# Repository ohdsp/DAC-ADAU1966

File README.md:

# [Open Hardware DSP Platform](http://www.ohdsp.org)
## ADAU1966 DAC with passive output filters
### Revision 2.0
###### DAC-ADAU1966 (KiCad 4.0.2-stable)
---
# README
### Disclaimer
Copyright Paul Janicki 2016

Licensed under the TAPR Open Hardware License (www.tapr.org/OHL)

This documentation is distributed WITHOUT ANY EXPRESS OR IMPLIED WARRANTY, INCLUDING OF MERCHANTABILITY, SATISFACTORY QUALITY AND FITNESS FOR A PARTICULAR PURPOSE.

### What is this repository? ###

**Quick summary**

This is a digital to analogue converter based on the ADAU1966 DAC chip from Analog Devices. This is designed as part the Open Hardware DSP Platform. This may or may not be suitable for use in other applications. 

This simple 16 channel DAC is designed to be used with 4xTDM4, 2xTDM8 or 1xTDM16 data inputs supported on devices such as the ADAU1452. This board can be used with the ADAU1966 in standalone mode (no host microcontroller needed) or with an external I2C interface to program/control the ADAU1966. The board uses only passive output filters on the ADAU1966 but can easily drive external PCBs through appropriate cabling.

This repository contains the KiCad design files, manufacturing Gerber/drill files, and PDF/drawing files for this board.

### What is the project folder structure?
Most folder names are self explanatory. Starting from the top level: \
*DAC-ADAU1966*
+ *Bill of Materials*  - This contains the bill of materials in CVS, LibreOffice Calc and XML formats
+ *Drawings*
    + *PCB* - This contains SVG and PDF outputs of PCB copper layers and assembly drawings
    + *Schematics* - This contains the PDF schematic drawing
+ *Gerbers* - This contains the PCB Gerbers and drill drawings for manufacture, there is also a zip file ready to send to most manufacturers
+ *KiCad* - This contains the original KiCad schematic and PCB design files

### How do I get set up? ###

**Summary of set up**

1. Set your self up a directory on a local disk, something simple will make life easier (eg C:\Electronics on Windows as used here), but anywhere will do just fine.
2. Download the Kicad-Libs from [https://github.com/ohdsp/KiCad-Libs](https://github.com/ohdsp/KiCad-Libs) and place in C:\Electronics\Kicad-Libs (or your chosen folder) 
3. Create a OHDSP subdirectory in C:\Electronics (so C:\Electronics\OHDSP)
3. Download this project to C:\Electronics\OHDSP\DAC-ADAU1966
4. Fire up Kicad
5. Open the main project file C:\Electronics\OHDSP\DAC-ADAU1966\Schematics\DAC-ADAU1966.pro
6. (Optional) Setup Pcbnew component library as below.
7. Do as you wish with the project, just keep it under the TAPR Open Hardware License.

Make sure your git setup doesn't exclude files used in the project (like .LIB files) or things may go wrong down the line.

**KiCad Library Configuration**

Note that you need to setup a Pcbnew library, but the eeschema libraries should work without any changes if you followed the instructions above.

To setup Pcbnew libraries:

In Pcbnew go to Preferences -> Footprint Libraries Manager. Under Global Libraries tab in the top list check if there is a nickname "MyKiCadLibs-Footprints" (usually at the end of the list). If there is but it points to the wrong place then change the Library Path to point to MyKiCadLibs-Footprints (eg C:\Electronics\KiCad-Libs\MyKiCadLibs-Footprints.pretty) folder for your setup. If this is missing you can use "Append with Wizard", choose "Files on my computer", click next, browse to library location (eg C:\Electronics\KiCad-Libs\MyKiCadLibs-Footprints.pretty) and select the folder MyKiCadLibs-Footprints.pretty, click next, check the Status column states OK and the Format is KiCad (if not re-download the library) and click next, then select "To global library configuration..." and click Finish.

To setup eeschema component libraries:
Either from KiCad project window go to Tools -> Run Library Editor OR under eeschema, go to Tools -> Library Editor. Then Preferences -> Component Libraries.

The top section "Component Library Files" should ideally contain only two libraries, the "power" library that ships with KiCad and "MyKiCadLibs-Lib" available from above. To setup MyKiCadLibs-Lib as a relative path under the "User defined search path" click add. Browse to the location of KiCad-Libs you download above (eg C:\Electronics\KiCad-Libs) and click "Select Folder". Say yes to add a relative path. Under component library files click add, browse to the KiCad-libs again (eg C:\Electronics\KiCad-Libs), select file "MyKiCadLibs-Lib.lib" and click open. MyKiCadLibs-lib should appear in the component library list with no path as it will be using the user defined search path set in the box below.

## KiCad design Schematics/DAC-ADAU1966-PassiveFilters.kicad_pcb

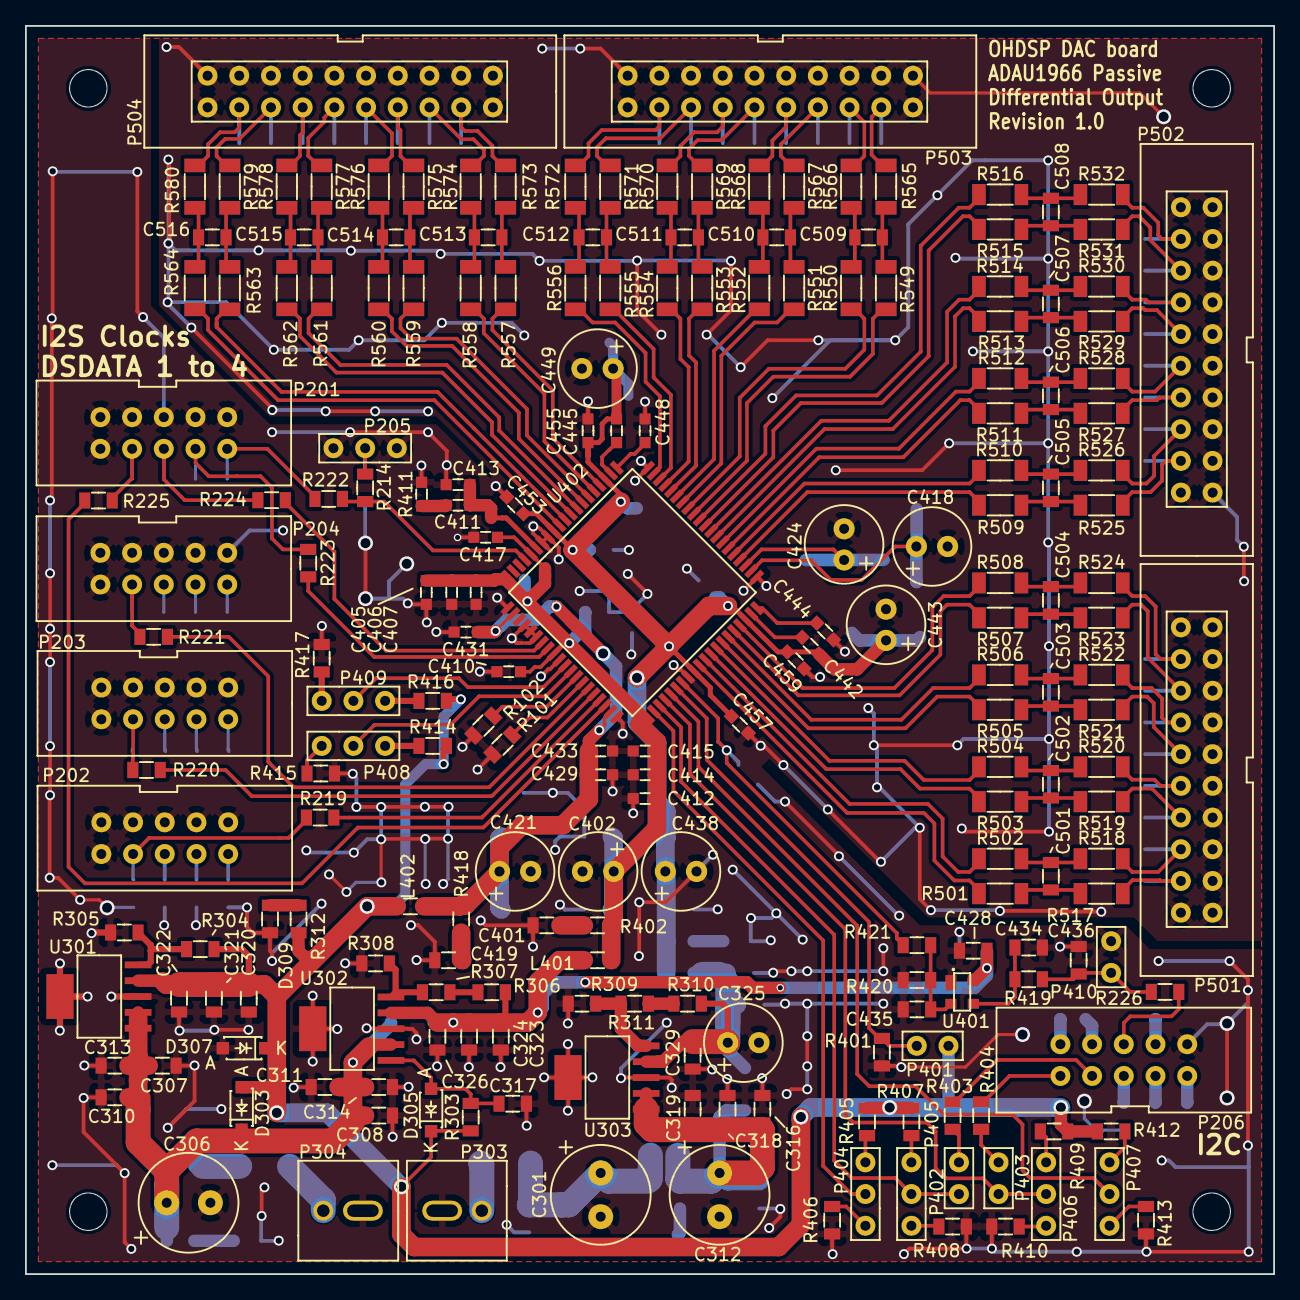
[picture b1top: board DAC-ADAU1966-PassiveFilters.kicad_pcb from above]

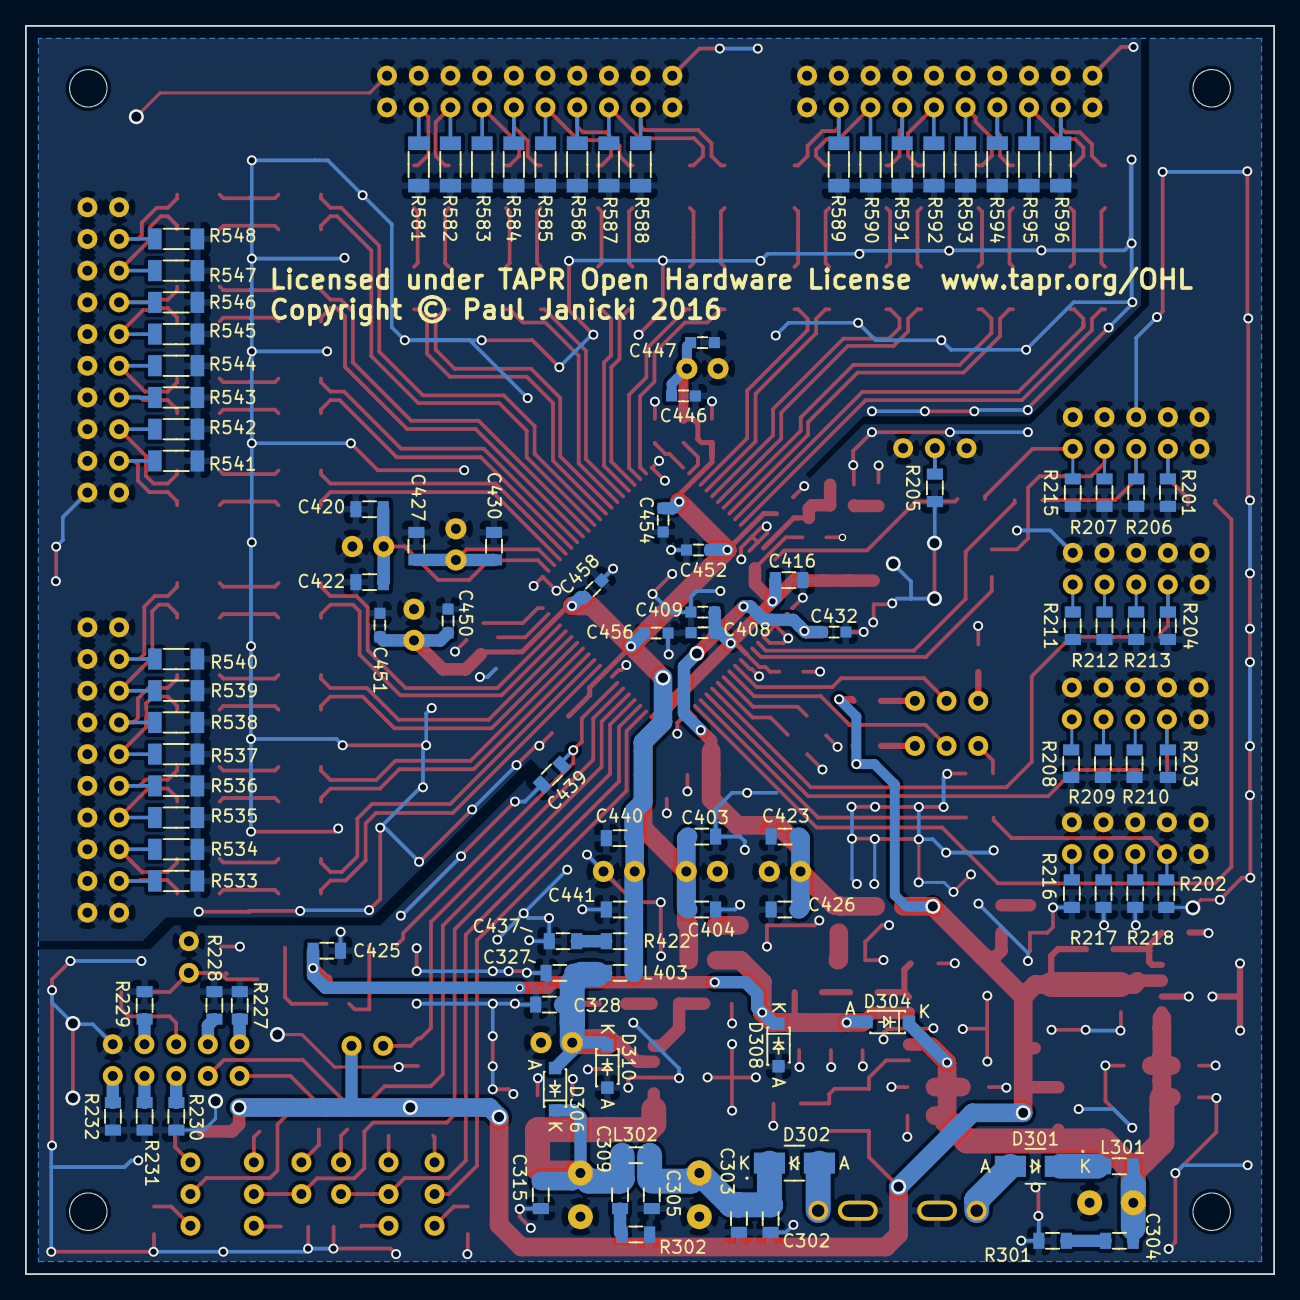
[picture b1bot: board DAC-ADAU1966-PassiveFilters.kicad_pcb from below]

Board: 2 copper layers, 100.0 x 100.0 mm, 314 parts (100 on the bottom side), 189 nets.

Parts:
C301, C306, C312: 220u; CAP-TH-D8mmP3.5mm
C302, C307, C308, C315, C317, C320, C323, C327, C403, C416, C420, C423, C427, C440: 22u; SMD-0805
C303, C310, C311, C316, C321, C324, C328, C404, C422, C426, C428, C430, C434, C435, C436, C439, C441: 100n; SMD-0805
C304, C309, C401, C419, C437: 100p; SMD-0805
C305, C313, C314, C318, C322, C326, C329: 10n; SMD-0805
C319: 1n; SMD-0805
C325, C402, C418, C421, C424, C438: 220u; CAP-TH-D6.3mmP2.5mm
C405, C408, C412, C429, C432, C452, C454, C456, C458: 1u; SMD-0603
C406, C409, C414, C417, C431, C433, C446, C450, C453, C455, C457, C459: 100n; SMD-0603
C407, C410, C415, C447, C451: 10n; SMD-0603
C411: 5n6; SMD-0603
C413: 390p; SMD-0603
C425: 1u; SMD-0805
C442, C444, C445, C448: 470n; SMD-0603
C443, C449: 47u; CAP-TH-D6.3mmP2.5mm
C501, C502, C503, C504, C505, C506, C507, C508, C509, C510, C511, C512, C513, C514, C515, C516: 2n7; SMD-0805
D301, D302: B230A; DIODE-SMA
D303, D304, D306, D307, D308, D310: SBR1A40S1; DIODE-SOD-123
D305: B130LAW-7-F; DIODE-SOD-123
D309: LED; SMD-0805
L301, L302, L401, L402, L403: 600R@100MHz; SMD-0805
P201, P202, P203, P204, P206: CONN_02X05; CONN_DIL_2X5_BOX
P205, P404, P405, P406, P407, P408, P409: CONN_3x1; CONN_SIL_3
P301, P302, P305, P306: PIN; MountingHole_3mm
P303, P304: CONN_2x1; CONN-2WAY-2.54mm-3.81mm-SPACING
P401, P402, P403, P410: CONN_2x1; CONN_SIL_2
P501, P502, P503, P504: CONN_02X10; CONN_DIL_2X10_BOX
R101, R102, R419: 1k; SMD-0805
R201, R202, R203, R204, R205, R206, R207, R214, R215, R305: N/F; SMD-0805
R208, R209, R210, R211, R212, R213, R216, R217, R218, R401, R405, R406, R407, R408, R409, R410, R412, R413, R414, R415, R416, R417: 10k; SMD-0805
R219, R220, R221, R222, R223, R224, R225, R226, R227, R228, R229, R230, R231, R232, R304, R310, R403, R404: 0R; SMD-0805
R301, R302, R402, R418, R422: 47R; SMD-0805
R303: 47k; SMD-0805
R306, R309: 2k2; SMD-0805
R307: 2k7; SMD-0805
R308: 4k7; SMD-0805
R311: 6k8; SMD-0805
R312: 470; SMD-0805
R411: 562R; SMD-0603
R420: 100k; SMD-0805
R421: 100R; SMD-0805
R501, R502, R503, R504, R505, R506, R507, R508, R509, R510, R511, R512, R513, R514, R515, R516, R549, R550, R551, R552, R553, R554, R555, R556, R557, R558, R559, R560, R561, R562, R563, R564: 240; SMD-1206
R517, R518, R519, R520, R521, R522, R523, R524, R525, R526, R527, R528, R529, R530, R531, R532, R565, R566, R567, R568, R569, R570, R571, R572, R573, R574, R575, R576, R577, R578, R579, R580: 100R; SMD-1206
R533, R534, R535, R536, R537, R538, R539, R540, R541, R542, R543, R544, R545, R546, R547, R548, R581, R582, R583, R584, R585, R586, R587, R588, R589, R590, R591, R592, R593, R594, R595, R596: 100k; SMD-1206
U301: TPS7A4533; IC-SOT223-6
U302, U303: TPS7A4501; IC-SOT223-6
U401: ADM811ZART; IC-SOT143
U402: IC-DAC-ADAU1966; IC-LQFP80-P065

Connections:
/ADAU1966/AVDD: C438.1, C440.1, C441.1, C442.1, C443.1, C445.1, C446.1, C447.1, C449.1, C450.1, C451.1, C452.1, C453.1, C454.1, C455.1, C456.1, C457.1, C458.1, C459.1, L403.2, R422.1, U402.3, U402.12, U402.49, U402.58
/ADAU1966/CCLK/SCL: P403.2, P406.2, U402.44
/ADAU1966/CDATA/ADDR1: P404.2, U402.42
/ADAU1966/COUT/SDA: P402.2, P405.2, U402.43
/ADAU1966/DACOUT_LRCLK: R223.2, U402.28
/ADAU1966/DACOUT_SDATA1: R225.2, U402.38
/ADAU1966/DACOUT_SDATA2: R219.2, U402.37
/ADAU1966/DACOUT_SDATA3: R220.2, U402.36
/ADAU1966/DACOUT_SDATA4: R221.2, U402.35
/ADAU1966/DACOUT_SDATA5: R101.1, U402.34
/ADAU1966/DACOUT_SDATA6: R102.1, U402.33
/ADAU1966/DAC_RESET: C439.1, R421.1, U402.47
/ADAU1966/DAC_SCL: P206.1, R404.1
/ADAU1966/DAC_SDA: P206.3, R403.1
/ADAU1966/DSDATA7: P408.2, U402.32
/ADAU1966/DSDATA8: P409.2, U402.31
/ADAU1966/DVDD: C402.1, C403.1, C404.1, C405.1, C406.1, C407.1, C408.1, C409.1, C410.1, C412.1, C414.1, C415.1, C416.1, C417.1, L401.2, R402.1, U402.16, U402.20, U402.29, U402.41
/ADAU1966/IOVDD: C421.1, C423.1, C426.1, C429.1, C431.1, C432.1, C433.1, L402.2, R418.1, U402.22, U402.39
/ADAU1966/LF: C411.1, C413.1, U402.15
/ADAU1966/MAN_RST_IN: C436.1, P410.1, R226.2, R419.2
/ADAU1966/MCLK: R214.2, R222.2, U402.17
/ADAU1966/OUT_1P: R501.1, U402.50
/ADAU1966/OUT_2P: R503.1, U402.52
/ADAU1966/OUT_3P: R505.1, U402.54
/ADAU1966/OUT_4P: R507.1, U402.56
/ADAU1966/OUT_5P: R509.1, U402.64
/ADAU1966/OUT_6P: R511.1, U402.66
/ADAU1966/OUT_7P: R513.1, U402.68
/ADAU1966/OUT_8P: R515.1, U402.70
/ADAU1966/OUT_9P: R549.1, U402.72
/ADAU1966/OUT_10P: R551.1, U402.74
/ADAU1966/OUT_11P: R553.1, U402.76
/ADAU1966/OUT_12P: R555.1, U402.78
/ADAU1966/OUT_13P: R557.1, U402.4
/ADAU1966/OUT_14P: R559.1, U402.6
/ADAU1966/OUT_15P: R561.1, U402.8
/ADAU1966/OUT_16P: R563.1, U402.10
/ADAU1966/SA: P401.2, R401.1, U402.46
/ADAU1966/~SS~/ADDR0: P407.2, U402.45
/AnaloguePassiveFilters/N1: R502.1, U402.51
/AnaloguePassiveFilters/N2: R504.1, U402.53
/AnaloguePassiveFilters/N3: R506.1, U402.55
/AnaloguePassiveFilters/N4: R508.1, U402.57
/AnaloguePassiveFilters/N5: R510.1, U402.65
/AnaloguePassiveFilters/N6: R512.1, U402.67
/AnaloguePassiveFilters/N7: R514.1, U402.69
/AnaloguePassiveFilters/N8: R516.1, U402.71
/AnaloguePassiveFilters/N9: R550.1, U402.73
/AnaloguePassiveFilters/N10: R552.1, U402.75
/AnaloguePassiveFilters/N11: R554.1, U402.77
/AnaloguePassiveFilters/N12: R556.1, U402.79
/AnaloguePassiveFilters/N13: R558.1, U402.5
/AnaloguePassiveFilters/N14: R560.1, U402.7
/AnaloguePassiveFilters/N15: R562.1, U402.9
/AnaloguePassiveFilters/N16: R564.1, U402.11
/Connectors/BCLK: R224.2, U402.27
GNDA: C301.2, C302.2, C303.2, C305.2, C306.2, C307.2, C308.2, C310.2, C311.2, C312.2, C313.2, C314.2, C315.2, C316.2, C317.2, C318.2, C319.2, C320.2, C321.2, C322.2, C323.2, C324.2, C325.2, C326.2, C327.2, C328.2, C329.2, C401.2, C402.2, C403.2, C404.2, C405.2, C406.2, C407.2, C408.2, C409.2, C410.2, C412.2, C413.2, C414.2, C415.2, C416.2, C417.2, C418.2, C419.2, C420.2, C421.2, C422.2, C423.2, C424.2, C425.2, C426.2, C427.2, C428.2, C429.2, C430.2, C431.2, C432.2, C433.2, C434.2, C435.2, C436.2, C437.2, C438.2, C439.2, C440.2, C441.2, C443.2, C444.2, C446.2, C447.2, C448.2, C449.2, C450.2, C451.2, C452.2, C453.2, C454.2, C455.2, C456.2, C457.2, C458.2, C459.2, D307.1, D308.1, D309.2, D310.1, P201.1, P201.3, P201.5, P201.7, P201.9, P201.10, P202.1, P202.3, P202.5, P202.7, P202.9, P202.10, P203.1, P203.3, P203.5, P203.7, P203.9, P203.10, P204.1, P204.3, P204.5, P204.7, P204.9, P204.10, P205.1, P205.3, P206.10, P303.2, P304.2, P410.2, P501.1, P501.2, P501.3, P501.5, P501.7, P501.9, P501.11, P501.13, P501.15, P501.17, P501.19, P501.20, P502.1, P502.2, P502.3, P502.5, P502.7, P502.9, P502.11, P502.13, P502.15, P502.17, P502.19, P502.20, P503.1, P503.2, P503.3, P503.5, P503.7, P503.9, P503.11, P503.13, P503.15, P503.17, P503.19, P503.20, P504.1, P504.2, P504.3, P504.5, P504.7, P504.9, P504.11, P504.13, P504.15, P504.17, P504.19, P504.20, R101.2, R102.2, R201.1, R202.1, R203.1, R204.1, R205.1, R206.1, R207.1, R208.2, R209.2, R210.2, R211.2, R212.2, R213.2, R215.1, R216.2, R217.2, R218.2, R227.2, R228.2, R229.2, R230.1, R231.1, R232.1, R301.2, R302.2, R305.1, R308.1, R309.2, R401.2, R406.2, R408.2, R410.2, R411.2, R413.2, R415.2, R417.2, R420.1, R533.2, R534.2, R535.2, R536.2, R537.2, R538.2, R539.2, R540.2, R541.2, R542.2, R543.2, R544.2, R545.2, R546.2, R547.2, R548.2, R581.2, R582.2, R583.2, R584.2, R585.2, R586.2, R587.2, R588.2, R589.2, R590.2, R591.2, R592.2, R593.2, R594.2, R595.2, R596.2, U301.3, U302.3, U303.3, U401.1, U402.13, U402.14, U402.21, U402.24, U402.25, U402.26, U402.30, U402.40, U402.48, U402.61, U402.80
unnamed: C301.1, C302.1, C303.1, C305.1, D302.2, L302.1
unnamed: C304.1, C306.1, C307.1, C308.1, C310.1, C311.1, C313.1, C314.1, D303.2, D304.2, L301.2, U301.1, U301.2, U302.2
unnamed: C304.2, R301.1
unnamed: C309.1, C312.1, C315.1, C316.1, C318.1, C319.1, D306.2, L302.2, U303.1, U303.2
unnamed: C309.2, R302.1
unnamed: C317.1, D305.1, R303.2, U302.1
unnamed: C401.1, R402.2
unnamed: C411.2, R411.1
unnamed: C418.1, C420.1, C422.1, U402.62
unnamed: C419.1, R418.2
unnamed: C424.1, C427.1, C430.1, U402.63
unnamed: C434.1, R419.1, U401.3
unnamed: C435.1, R420.2, R421.2, U401.2
unnamed: C437.1, R422.2
unnamed: C442.2, U402.59
unnamed: C444.1, U402.60
unnamed: C445.2, U402.2
unnamed: C448.1, U402.1
unnamed: C501.1, R502.2, R518.1
unnamed: C501.2, R501.2, R517.1
unnamed: C502.1, R504.2, R520.1
unnamed: C502.2, R503.2, R519.1
unnamed: C503.1, R506.2, R522.1
unnamed: C503.2, R505.2, R521.1
unnamed: C504.1, R508.2, R524.1
unnamed: C504.2, R507.2, R523.1
unnamed: C505.1, R510.2, R526.1
unnamed: C505.2, R509.2, R525.1
unnamed: C506.1, R512.2, R528.1
unnamed: C506.2, R511.2, R527.1
unnamed: C507.1, R514.2, R530.1
unnamed: C507.2, R513.2, R529.1
unnamed: C508.1, R516.2, R532.1
unnamed: C508.2, R515.2, R531.1
unnamed: C509.1, R550.2, R566.1
unnamed: C509.2, R549.2, R565.1
unnamed: C510.1, R552.2, R568.1
unnamed: C510.2, R551.2, R567.1
unnamed: C511.1, R554.2, R570.1
unnamed: C511.2, R553.2, R569.1
unnamed: C512.1, R556.2, R572.1
unnamed: C512.2, R555.2, R571.1
unnamed: C513.1, R558.2, R574.1
unnamed: C513.2, R557.2, R573.1
unnamed: C514.1, R560.2, R576.1
unnamed: C514.2, R559.2, R575.1
unnamed: C515.1, R562.2, R578.1
unnamed: C515.2, R561.2, R577.1
unnamed: C516.1, R564.2, R580.1
unnamed: C516.2, R563.2, R579.1
unnamed: D301.1, P304.1
unnamed: D301.2, L301.1
unnamed: D302.1, P303.1
unnamed: D309.1, R312.1
unnamed: P201.2, R215.2, R222.1
unnamed: P201.4, R207.2, R223.1
unnamed: P201.6, R206.2, R224.1
unnamed: P201.8, R201.2, R225.1
unnamed: P202.2, R216.1
unnamed: P202.4, R217.1
unnamed: P202.6, R218.1
unnamed: P202.8, R202.2, R219.1
unnamed: P203.2, R208.1
unnamed: P203.4, R209.1
unnamed: P203.6, R210.1
unnamed: P203.8, R203.2, R220.1
unnamed: P204.2, R211.1
unnamed: P204.4, R212.1
unnamed: P204.6, R213.1
unnamed: P204.8, R204.2, R221.1
unnamed: P205.2, R205.2, R214.1
unnamed: P206.2, R227.1
unnamed: P206.4, R228.1
unnamed: P206.5, R230.2
unnamed: P206.6, R226.1
unnamed: P206.7, R231.2
unnamed: P206.8, R229.1
unnamed: P206.9, R232.2
unnamed: P402.1, R403.2
unnamed: P403.1, R404.2
unnamed: P404.1, R405.2
unnamed: P404.3, R406.1
unnamed: P405.1, R407.2
unnamed: P405.3, R408.1
unnamed: P406.1, R409.2
unnamed: P406.3, R410.1
unnamed: P407.1, R412.2
unnamed: P407.3, R413.1
unnamed: P408.1, R414.2
unnamed: P408.3, R415.1
unnamed: P409.1, R416.2
unnamed: P409.3, R417.1
unnamed: P501.4, R517.2, R533.1
unnamed: P501.6, R518.2, R534.1
unnamed: P501.8, R519.2, R535.1
unnamed: P501.10, R520.2, R536.1
unnamed: P501.12, R521.2, R537.1
unnamed: P501.14, R522.2, R538.1
unnamed: P501.16, R523.2, R539.1
unnamed: P501.18, R524.2, R540.1
unnamed: P502.4, R525.2, R541.1
unnamed: P502.6, R526.2, R542.1
unnamed: P502.8, R527.2, R543.1
unnamed: P502.10, R528.2, R544.1
unnamed: P502.12, R529.2, R545.1
unnamed: P502.14, R530.2, R546.1
unnamed: P502.16, R531.2, R547.1
unnamed: P502.18, R532.2, R548.1
unnamed: P503.4, R565.2, R581.1
unnamed: P503.6, R566.2, R582.1
unnamed: P503.8, R567.2, R583.1
unnamed: P503.10, R568.2, R584.1
unnamed: P503.12, R569.2, R585.1
unnamed: P503.14, R570.2, R586.1
unnamed: P503.16, R571.2, R587.1
unnamed: P503.18, R572.2, R588.1
unnamed: P504.4, R573.2, R589.1
unnamed: P504.6, R574.2, R590.1
unnamed: P504.8, R575.2, R591.1
unnamed: P504.10, R576.2, R592.1
unnamed: P504.12, R577.2, R593.1
unnamed: P504.14, R578.2, R594.1
unnamed: P504.16, R579.2, R595.1
unnamed: P504.18, R580.2, R596.1
unnamed: R304.2, R305.2, U301.5
unnamed: R306.1, R307.1
unnamed: R307.2, R308.2, U302.5
unnamed: R309.1, R311.2, U303.5
unnamed: R310.1, R311.1
VAA: C325.1, C327.1, C328.1, C329.1, D306.1, D310.2, L403.1, R310.2, U303.4
VDD: C323.1, C324.1, C326.1, C425.1, C428.1, D304.1, D308.2, L401.1, R306.2, U302.4, U401.4
VPP: C320.1, C321.1, C322.1, D303.1, D305.2, D307.2, L402.1, P401.1, R303.1, R304.1, R312.2, R405.1, R407.1, R409.1, R412.1, R414.1, R416.1, U301.4

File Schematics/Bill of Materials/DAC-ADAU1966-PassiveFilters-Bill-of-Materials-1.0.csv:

,"DAC-ADAU1966-PassiveFilters Bill of Materials Release 1.0",,,,,,
,"24/01/16",,,,,,
"Id","Designator","Package","Quantity","Designation","Detail",,
1,"D303,D304,D306,D307,D308,D310","DIODE-SOD-123",6,"SBR1A40S1","Diodes Inc. SBR1A40S1",,
2,"C308,C440,C423,C427,C420,C416,C403,C327,C323,C320,C307,C302,C315,C317","SMD-0805",14,"22u","25V X5R 20%",,
3,"R304,R404,R403,R310,R226,R220,R221,R225,R224,R223,R222,R219,R227,R228,R229,R230,R231,R232","SMD-0805",18,"0R","100mW",,
4,"R308","SMD-0805",1,"4k7","100mW",,
5,"P204,P202,P201,P203,P206","CONN_DIL_2X5_BOX",5,"CONN_02X05","2x5 2.54mm box header",,
6,"P306,P305,P302,P301","MountingHole_3mm",4,"PIN","Mounting hole only",,
7,"D302,D301","DIODE-SMA",2,"B230A","Diodes Inc. B230A-13-F",,
8,"P410,P403,P402,P401","CONN_SIL_2",4,"CONN_2x1","P401-P403 2.54mm pitch pin header (jumper), P410 can wire directly",,
9,"C516,C515,C514,C513,C512,C511,C510,C509,C508,C507,C506,C505,C504,C503,C502,C501","SMD-0805",16,"2n7","50V NP0 5%",,
10,"R562,R561,R560,R559,R558,R557,R556,R555,R554,R553,R552,R551,R550,R549,R516,R515,R514,R513,R512,R511,R510,R509,R508,R507,R506,R505,R504,R503,R564,R563,R502,R501","SMD-1206",32,"240","MELF 0204",,
11,"R548,R547,R546,R545,R544,R543,R542,R541,R540,R539,R538,R537,R536,R535,R596,R595,R594,R593,R592,R591,R590,R589,R588,R587,R586,R585,R584,R583,R582,R581,R534,R533","SMD-1206",32,"100k","MELF 0204",,
12,"R532,R531,R530,R529,R528,R527,R526,R525,R524,R523,R522,R521,R520,R519,R580,R579,R578,R577,R576,R575,R574,R573,R572,R571,R570,R569,R568,R567,R566,R565,R518,R517","SMD-1206",32,"100R","MELF 0204",,
13,"R411","SMD-0603",1,"562R","63mW",,
14,"C433,C459,C457,C455,C453,C431,C417,C414,C409,C406,C446,C450","SMD-0603",12,"100n","50V X7R 10%",,
15,"C458,C456,C454,C452,C432,C429,C412,C408,C405","SMD-0603",9,"1u","16V X7R 10%",,
16,"C448,C445,C444,C442","SMD-0603",4,"470n","25V X7R 10%",,
17,"C415,C410,C407,C447,C451","SMD-0603",5,"10n","50V X7R 10%",,
18,"C413","SMD-0603",1,"390p","50V NP0 5%",,
19,"C411","SMD-0603",1,"5n6","50V X7R 10%",,
20,"C441,C439,C436,C435,C434,C426,C430,C428,C422,C404,C328,C324,C321,C316,C311,C310,C303","SMD-0805",17,"100n","50V X7R 10%",,
21,"U402","IC-LQFP80-P065",1,"IC-DAC-ADAU1966","Analog Devices ADAU1966WBSTZ DAC",,
22,"U401","IC-SOT143",1,"ADM811ZART","Analog Devices ADM811ZART Supervisor",,
23,"U303,U302","IC-SOT223-6",2,"TPS7A4501","Texas Instruments TPS7A4501DCQT low noise regulator",,
24,"U301","IC-SOT223-6",1,"TPS7A4533","Texas Instruments TPS7A4533DCQT low noise regulator",,
25,"R422,R418,R402,R302,R301","SMD-0805",5,"47R","100mW",,
26,"R421","SMD-0805",1,"100R","100mW",,
27,"R420","SMD-0805",1,"100k","100mW",,
28,"R419,R102,R101","SMD-0805",3,"1k","100mW",,
29,"R417,R416,R415,R414,R413,R412,R410,R409,R408,R407,R406,R405,R401,R216,R217,R218,R211,R212,R213,R208,R209,R210","SMD-0805",22,"10k","100mW",,
30,"R309,R306","SMD-0805",2,"2k2","100mW",,
31,"R311","SMD-0805",1,"6k8","100mW",,
32,"R307","SMD-0805",1,"2k7","100mW",,
33,"R305,R203,R204,R207,R206,R201,R202,R215,R214,R205","SMD-0805",10,"N/F","NOT FITTED",,
34,"P409,P408,P407,P406,P405,P404,P205","CONN_SIL_3",7,"CONN_3x1","P404-P409 2.54mm pitch pin header (jumper), P205 can wire directly",,
35,"P304,P303","CONN-2WAY-2.54mm-3.81mm-SPACING",2,"CONN_2x1","Any 2.54mm  or 3.81mm screw terminal eg CamdenBoss CTB0308/2",,
36,"L403,L402,L401,L302,L301","SMD-0805",5,"600R@100MHz","'=>1A eg Wruth 742792040, TDK MPZ2012S601A",,
37,"C437,C419,C401,C309,C304","SMD-0805",5,"100p","50V NP0 5%",,
38,"C425","SMD-0805",1,"1u","25V X7R 10%",,
39,"C329,C326,C322,C314,C313,C305,C318","SMD-0805",7,"10n","50V X7R 10%",,
40,"C319","SMD-0805",1,"1n","50V X7R 10%",,
41,"C306,C301,C312","CAP-TH-D8mmP3.5mm",3,"220u","'=>25V eg Panasonic EEU-FC1V221L",,
42,"P501,P502,P503,P504","CONN_DIL_2X10_BOX",4,"CONN_02X10","2x10 2.54mm box header",,
43,"C421,C325,C402,C418,C424,C438","CAP-TH-D6.3mmP2.5mm",6,"220u","'=>16V eg Panasonic EEU-FR1C221",,
44,"C449,C443","CAP-TH-D6.3mmP2.5mm",2,"47u","'=>16V eg Panasonic EEUFR1H470",,
45,"R303","SMD-0805",1,"47k","100mW",,
46,"D305","DIODE-SOD-123",1,"B130LAW-7-F","Diodes Inc B130LAW-7-F Vf=380mV",,
47,"R312","SMD-0805",1,"470","100mW",,
48,"D309","SMD-0805",1,"LED","Green or Red 0805 LED eg Avago HSMC-C170",,

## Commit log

2016-01-24 Release 1.0
    Release 1.0
2016-05-26 Revision 2.0
2016-07-01 Revision 2.0
    Minor readme website link update
2016-07-01 Revision 2.0
    Update BOM sheet name

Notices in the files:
Schematics/DAC-ADAU1966-PassiveFilters.kicad_pcb:
Licensed under TAPR Open Hardware License  www.tapr.org/OHL
Copyright © Paul Janicki 2016
